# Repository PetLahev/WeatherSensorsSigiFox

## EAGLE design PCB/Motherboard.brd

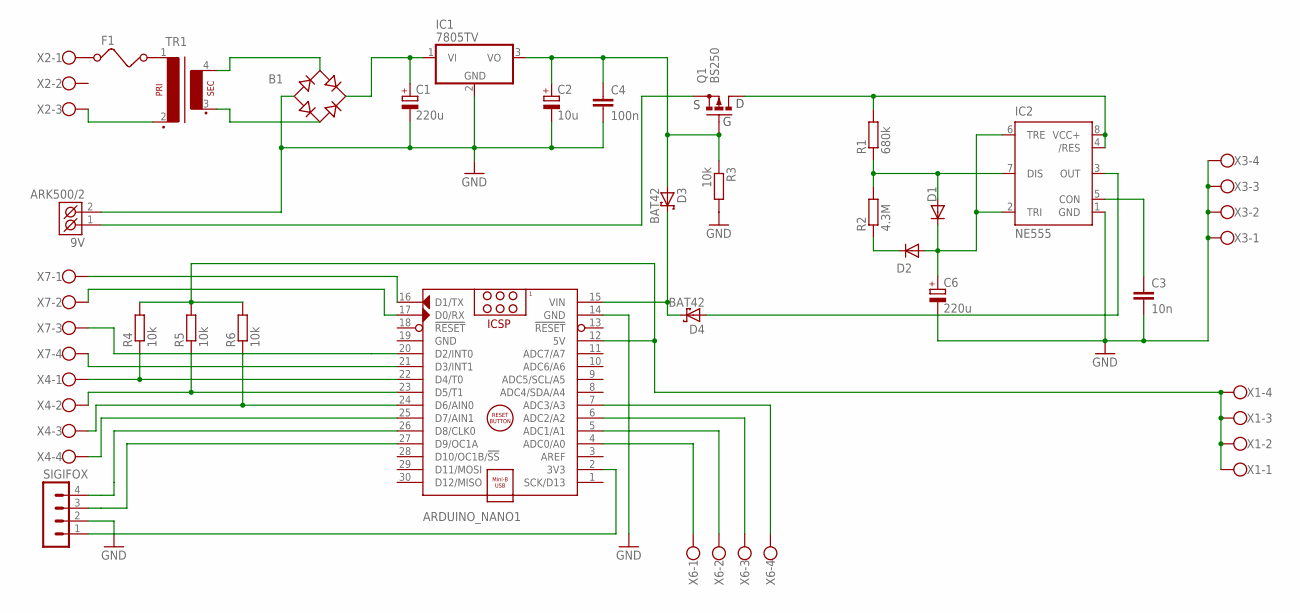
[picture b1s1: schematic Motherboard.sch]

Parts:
9V: ARK500/2
ARDUINO_NANO1: ARDUINO_NANO
B1: RECTIFIER-RB1A; RB1A
C1, C6: 220u; E5-13
C2: 10u; E2,5-6E
C3: 10n; C2.5-2
C4: 100n; C2.5-2
D1, D2: 1N4148DO35-7; DO35-7
D3, D4: BAT42; DO35-10
F1: FUSE
IC1: 7805TV; TO220V
IC2: NE555; DIL-08
Q1: BS250; SOT54E
R1: 680k; 0207/5V
R2: 4.3M; 0207/5V
R3: 10k; 0207/5V
R4, R5, R6: 10k; 0207/7
SIGIFOX: MA04-1
TR1: VP31
X1, X3, X4, X6, X7: W237-4
X2: W237-103

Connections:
3V3: ARDUINO_NANO1.2 (3V3), SIGIFOX.1
5V: ARDUINO_NANO1.12 (5V), R4.2, R5.2, R6.2, X1.1, X1.2, X1.3, X1.4
9VN: B1.+, C1.+, IC1.1 (VI)
A0: ARDUINO_NANO1.4 (ADC0/A0), X6.1
A1: ARDUINO_NANO1.5 (ADC1/A1), X6.2
A2: ARDUINO_NANO1.6 (ADC2/A2), X6.3
A3: ARDUINO_NANO1.7 (ADC3/A3), X6.4
D2: ARDUINO_NANO1.20 (D2/INT0), X7.3
D3: ARDUINO_NANO1.21 (D3/INT1), X7.4
D4: ARDUINO_NANO1.22 (D4/T0), R4.1, X4.1
D5: ARDUINO_NANO1.23 (D5/T1), R5.1, X4.2
D6: ARDUINO_NANO1.24 (D6/AIN0), R6.1, X4.3
D7: ARDUINO_NANO1.25 (D7/AIN1), X4.4
G: C2.+, C4.1, D3.A, IC1.3 (VO), Q1.G, R3.1
GND: 9V.2 (K2), ARDUINO_NANO1.14 (GND), ARDUINO_NANO1.19 (GND), B1.-, C1.-, C2.-, C3.2, C4.2, C6.-, IC1.2 (GND), IC2.1 (GND), R3.2, SIGIFOX.2, X3.1, X3.2, X3.3, X3.4
unnamed: D4.A, IC2.3 (OUT)
unnamed: F1.2, TR1.1
unnamed: D1.A, IC2.7 (DIS), R1.1, R2.2
unnamed: C6.+, D1.C, D2.A, IC2.2 (TRI), IC2.6 (TRE)
unnamed: C3.1, IC2.5 (CON)
unnamed: D2.C, R2.1
unnamed: F1.1, X2.1
unnamed: B1.AC1, TR1.4 (S4)
unnamed: B1.AC2, TR1.3 (S3)
unnamed: TR1.2, X2.3
unnamed: ARDUINO_NANO1.15 (VIN), D3.C, D4.C
RX: ARDUINO_NANO1.17 (D0/RX), X7.2
S: 9V.1 (K1), Q1.S
SIGIFOX_RX: ARDUINO_NANO1.27 (D9/OC1A), SIGIFOX.3
SIGIFOX_TX: ARDUINO_NANO1.26 (D8/CLK0), SIGIFOX.4
TX: ARDUINO_NANO1.16 (D1/TX), X7.1
VCC: IC2.4 (/RES), IC2.8 (VCC+), Q1.D, R1.2

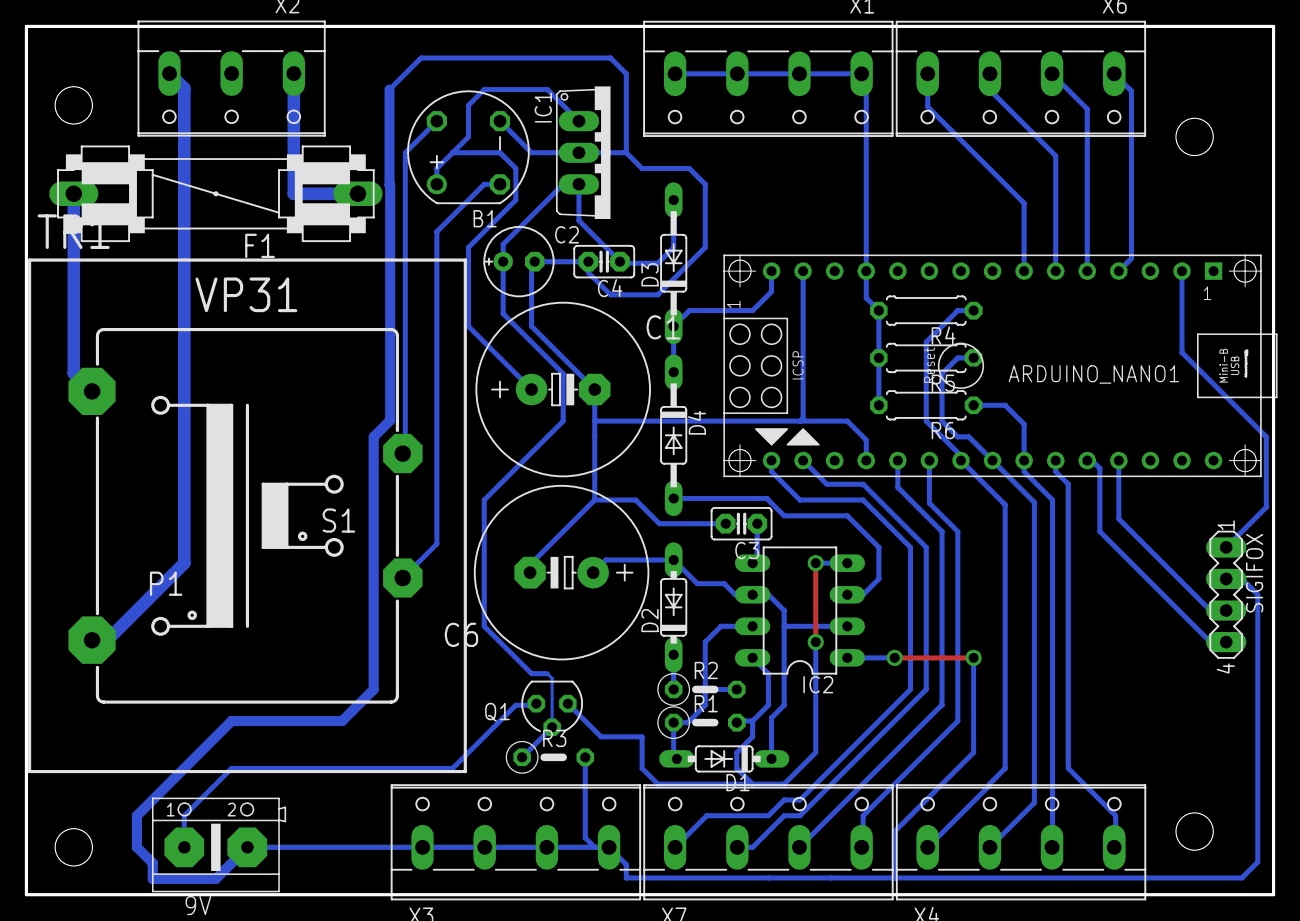
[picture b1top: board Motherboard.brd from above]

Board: 2 copper layers, 100.3 x 69.8 mm, 30 parts (0 on the bottom side), 32 nets.

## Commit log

2020-08-30 Added scheme and PCB
2020-09-02 First version. Should be fully working. It's was running for 24 hours.
2020-09-10 Added second sensor outside the court. Given the physical condition is on separate pin
2020-09-10 Renamed some signals
2020-09-10 Uncomented commands for sending sigfox
2020-09-11 Fixed bugs with reading sensor and labeling connectors

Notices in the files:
parts and their libraries:
Copyright (C) PaJa 2011-2014
